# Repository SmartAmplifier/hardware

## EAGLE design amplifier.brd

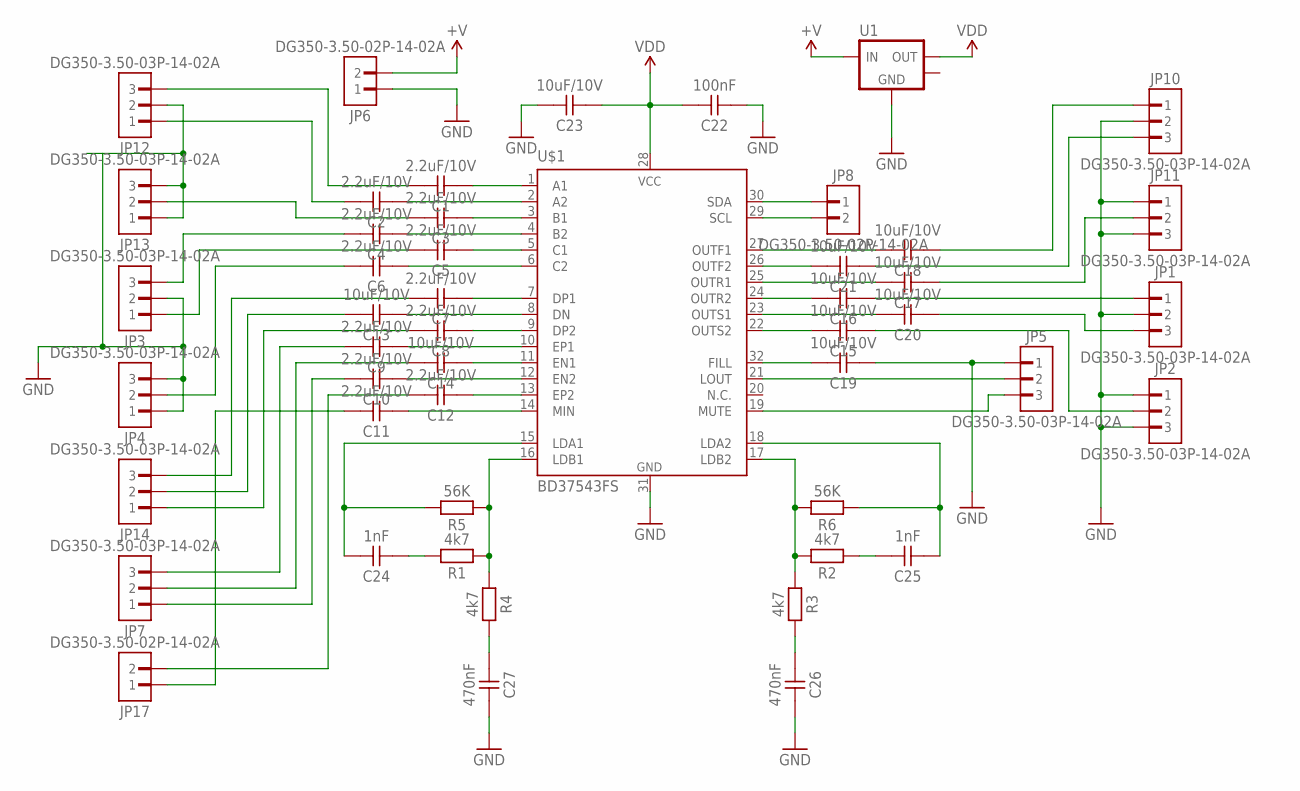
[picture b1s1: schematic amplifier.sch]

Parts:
C1, C2, C3, C4, C5, C6, C7, C8, C9, C10, C11, C12: 2.2uF/10V; CAPACITOR-0805_R
C13, C14, C15, C16, C17, C18, C19, C20, C21, C23: 10uF/10V; CAPACITOR-0805_R
C22: 100nF; CAPACITOR-0805_R
C24, C25: 1nF; CAPACITOR-0805_R
C26, C27: 470nF; CAPACITOR-0805_R
JP1, JP2, JP3, JP4, JP5, JP7, JP10, JP11, JP12, JP13, JP14: DG350-3.50-03P-14-02A; DG350-3.50-03P-14-02A_T
JP6, JP8, JP17: DG350-3.50-02P-14-02A; DG350-3.50-02P-14-02A_T
R1, R2, R3, R4: 4k7; RESISTOR-0805_R
R5, R6: 56K; RESISTOR-0805_R
U1: LM2940KTT; TO263-3
U$1: BD37543FS; SSOP32

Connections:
+V: JP6.2, U1.1 (VIN)
GND: C19.2, C22.2, C23.1, C26.1, C27.1, JP1.2, JP2.1, JP2.3, JP3.2, JP4.1, JP4.3, JP5.1, JP6.1, JP10.2, JP11.1, JP11.3, JP12.2, JP13.1, JP13.3, U1.2 (GND), U$1.31 (GND)
unnamed: C1.2, U$1.1 (A1)
unnamed: C2.2, U$1.2 (A2)
unnamed: C3.2, U$1.3 (B1)
unnamed: C4.2, U$1.4 (B2)
unnamed: C5.2, U$1.5 (C1)
unnamed: C6.2, U$1.6 (C2)
unnamed: C7.2, U$1.7 (DP1)
unnamed: C13.2, U$1.8 (DN)
unnamed: C8.2, U$1.9 (DP2)
unnamed: C11.2, U$1.14 (MIN)
unnamed: C12.2, U$1.13 (EP2)
unnamed: C10.2, U$1.12 (EN2)
unnamed: C14.2, U$1.11 (EN1)
unnamed: C9.2, U$1.10 (EP1)
unnamed: C19.1, U$1.32 (FILL)
unnamed: C15.1, U$1.22 (OUTS2)
unnamed: C16.1, U$1.24 (OUTR2)
unnamed: C17.1, U$1.25 (OUTR1)
unnamed: C21.1, U$1.26 (OUTF2)
unnamed: C18.1, U$1.27 (OUTF1)
unnamed: R1.1, R4.1, R5.1, U$1.16 (LDB1)
unnamed: C24.1, R5.2, U$1.15 (LDA1)
unnamed: R2.2, R3.1, R6.2, U$1.17 (LDB2)
unnamed: C25.2, R6.1, U$1.18 (LDA2)
unnamed: C24.2, R1.2
unnamed: C27.2, R4.2
unnamed: C25.1, R2.1
unnamed: C26.2, R3.2
unnamed: JP8.1, U$1.30 (SDA)
unnamed: JP8.2, U$1.29 (SCL)
unnamed: JP5.2, U$1.21 (LOUT)
unnamed: C11.1, JP17.1
unnamed: C15.2, JP2.2
unnamed: C20.2, JP1.3
unnamed: C16.2, JP1.1
unnamed: C20.1, U$1.23 (OUTS1)
unnamed: C17.2, JP11.2
unnamed: C21.2, JP10.3
unnamed: C18.2, JP10.1
unnamed: C1.1, JP12.3
unnamed: C2.1, JP12.1
unnamed: C3.1, JP13.2
unnamed: C4.1, JP3.3
unnamed: C5.1, JP3.1
unnamed: C6.1, JP4.2
unnamed: C7.1, JP14.3
unnamed: C13.1, JP14.2
unnamed: C8.1, JP14.1
unnamed: C9.1, JP7.3
unnamed: C14.1, JP7.2
unnamed: C10.1, JP7.1
unnamed: JP5.3, U$1.19 (MUTE)
unnamed: C12.1, JP17.2
VDD: C22.1, C23.2, U1.3 (VOUT), U$1.28 (VCC)

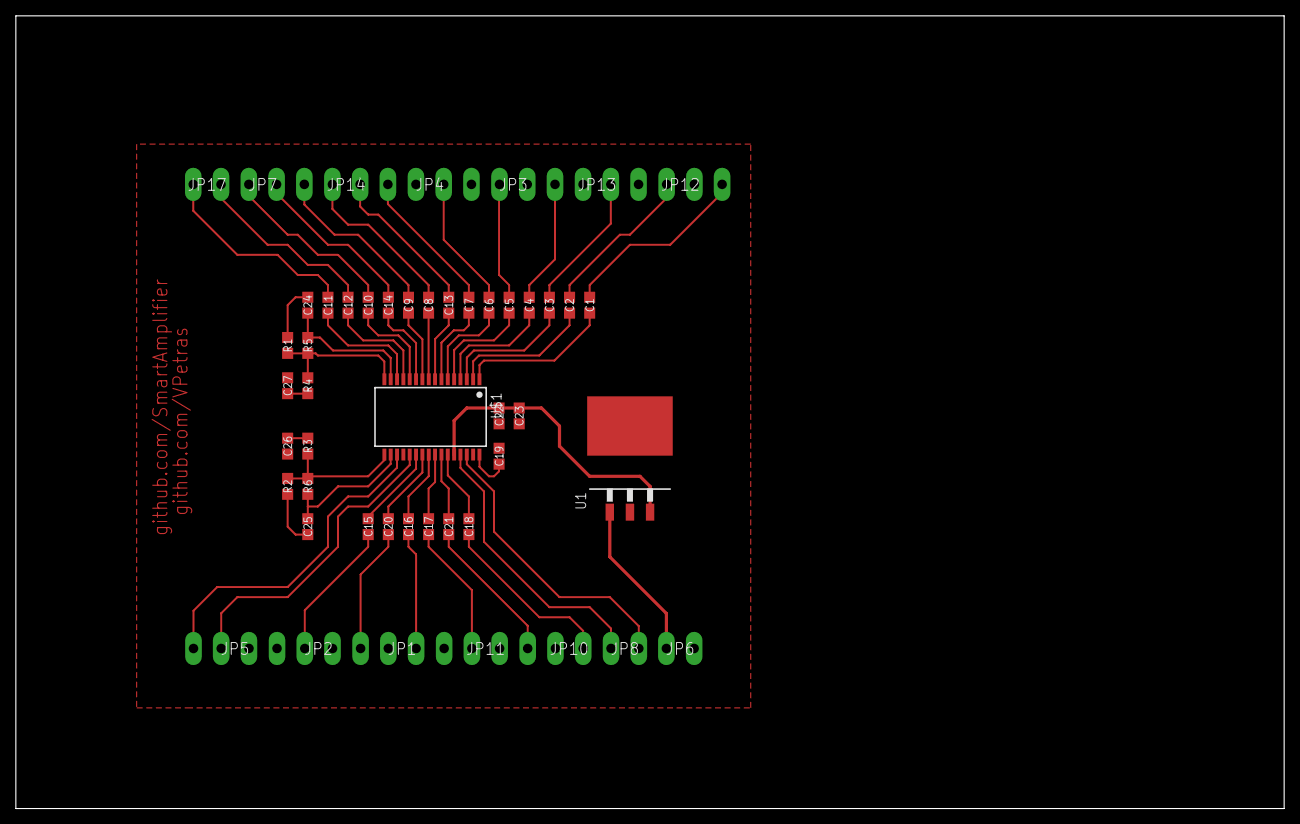
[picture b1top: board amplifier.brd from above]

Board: 2 copper layers, 160.0 x 100.0 mm, 49 parts (0 on the bottom side), 56 nets.
